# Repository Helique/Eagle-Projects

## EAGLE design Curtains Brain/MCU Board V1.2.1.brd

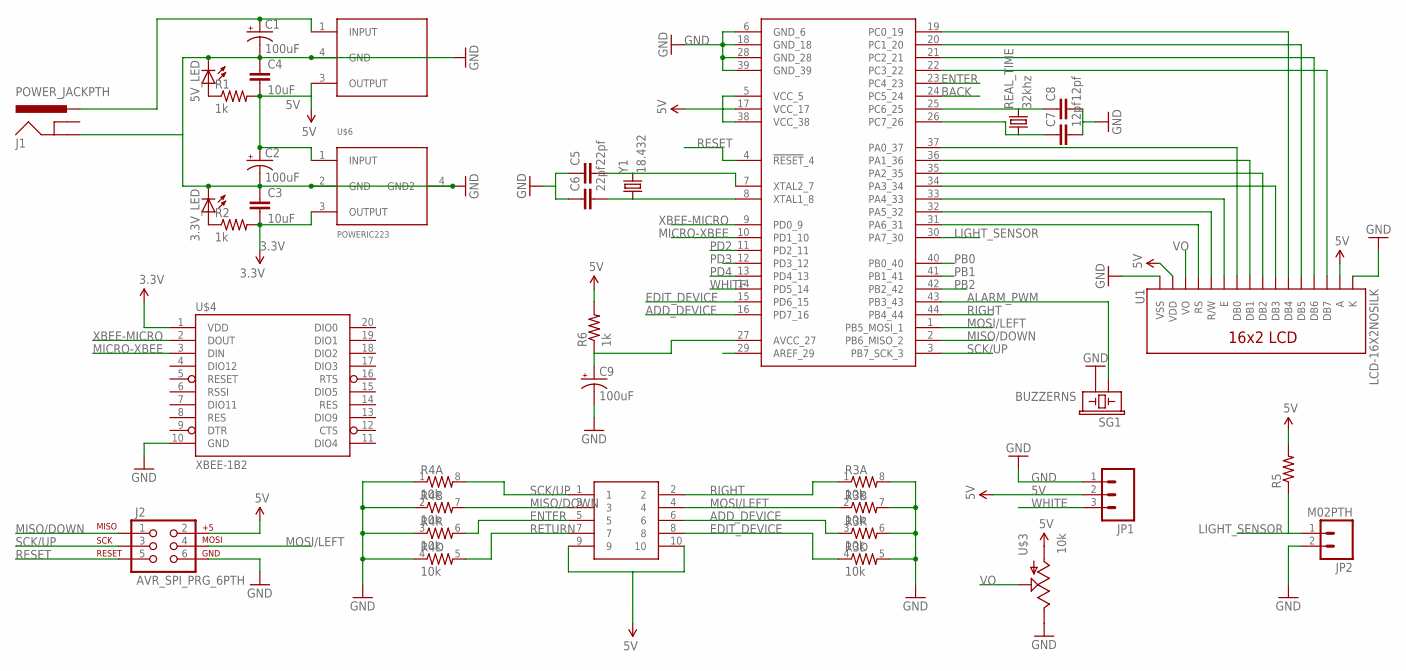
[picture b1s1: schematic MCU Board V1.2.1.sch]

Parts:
3.3V_LED, 5V_LED: LED1206; LED-1206
C1, C2, C9: 100uF; PANASONIC_D
C3, C4: 10uF; 1206
C5, C6: 22pf; 0805
C7, C8: 12pf; 0805
J1: POWER_JACKPTH; POWER_JACK_PTH
J2: AVR_SPI_PRG_6PTH; 2X3
JP1: M03PTH; 1X03
JP2: M02PTH; 1X02
R1, R2, R6: 1k; 1206
R3, R4: 10k; 0603-ARV
R5: RESISTOR1206; 1206
REAL_TIME: 32khz; TC26H
SG1: BUZZERNS; BUZZER-12MM-NS
U1: LCD-16X2NOSILK; LCD-16X2_NOSILK
U$1: ATMEGA1284; TQFP44
U$2: 10PIN_HEADER_MALETHROUGH-HOLE; 2X5-SHROUDED
U$3: 10k; TRIM_POT
U$4: XBEE-1B2; XBEE-SILK
U$5: DPACK_V_REG; DPAK
U$6: POWERIC223; SOT223
Y1: 18.432; HC49US

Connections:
3.3V: C3.2, R2.2, U$4.1 (VDD), U$6.3 (OUTPUT)
5V: C2.+, C4.2, J2.2, JP1.2, R1.2, R5.2, R6.2, U1.2 (VDD), U1.15 (A), U$1.5 (VCC_5), U$1.17 (VCC_17), U$1.38 (VCC_38), U$2.9, U$2.10, U$3.3 (A), U$5.3 (OUTPUT), U$6.1 (INPUT)
ADD_DEVICE: R3.3 (1), U$1.16 (PD7_16), U$2.6
ALARM_PWM: SG1.+ (1), U$1.43 (PB3_43)
AREF: U$1.29 (AREF_29)
BACK: U$1.24 (PC5_24)
EDIT_DEVICE: R3.4 (1), U$1.15 (PD6_15), U$2.8
ENTER: R4.6 (2), U$1.23 (PC4_23), U$2.5
GND: 3.3V_LED.C, 5V_LED.C, C1.-, C2.-, C3.1, C4.1, C5.1, C6.1, C7.2, C8.2, C9.-, J1.GND, J2.6, JP1.1, JP2.2, R3.5 (2), R3.6 (2), R3.7 (2), R3.8 (2), R4.1, R4.2 (1), R4.3 (1), R4.4 (1), SG1.- (2), U1.1 (VSS), U1.16 (K), U$1.6 (GND_6), U$1.18 (GND_18), U$1.28 (GND_28), U$1.39 (GND_39), U$3.2 (E), U$4.10 (GND), U$5.4 (GND), U$6.2 (GND), U$6.4 (GND2)
LIGHT_SENSOR: JP2.1, R5.1, U$1.30 (PA7_30)
MICRO-XBEE: U$1.10 (PD1_10), U$4.3 (DIN)
MISO/DOWN: J2.1, R4.7 (2), U$1.2 (PB6_MISO_2), U$2.3
MOSI/LEFT: J2.4, R3.2 (1), U$1.1 (PB5_MOSI_1), U$2.4
unnamed: C7.1, REAL_TIME.1, U$1.26 (PC7_26)
unnamed: C5.2, U$1.7 (XTAL2_7), Y1.2
unnamed: C6.2, U$1.8 (XTAL1_8), Y1.1
unnamed: C8.1, REAL_TIME.2, U$1.25 (PC6_25)
unnamed: 5V_LED.A, R1.1
unnamed: 3.3V_LED.A, R2.1
unnamed: U1.7 (DB0), U$1.37 (PA0_37)
unnamed: U1.8 (DB1), U$1.36 (PA1_36)
unnamed: U1.9 (DB2), U$1.35 (PA2_35)
unnamed: U1.10 (DB3), U$1.34 (PA3_34)
unnamed: U1.6 (E), U$1.33 (PA4_33)
unnamed: U1.5 (R/W), U$1.32 (PA5_32)
unnamed: U1.4 (RS), U$1.31 (PA6_31)
unnamed: U1.11 (DB4), U$1.19 (PC0_19)
unnamed: U1.12 (DB5), U$1.20 (PC1_20)
unnamed: U1.13 (DB6), U$1.21 (PC2_21)
unnamed: U1.14 (DB7), U$1.22 (PC3_22)
unnamed: C9.+, R6.1, U$1.27 (AVCC_27)
PB0: U$1.40 (PB0_40)
PB1: U$1.41 (PB1_41)
PB2: U$1.42 (PB2_42)
PD2: U$1.11 (PD2_11)
PD3: U$1.12 (PD3_12)
PD4: U$1.13 (PD4_13)
PWR: C1.+, J1.PWR, U$5.1 (INPUT)
RESET: J2.5, U$1.4 (!RESET!_4)
RETURN: R4.5 (2), U$2.7
RIGHT: R3.1, U$1.44 (PB4_44), U$2.2
SCK/UP: J2.3, R4.8 (2), U$1.3 (PB7_SCK_3), U$2.1
VO: U1.3 (VO), U$3.1 (S)
WHITE: JP1.3, U$1.14 (PD5_14)
XBEE-MICRO: U$1.9 (PD0_9), U$4.2 (DOUT)

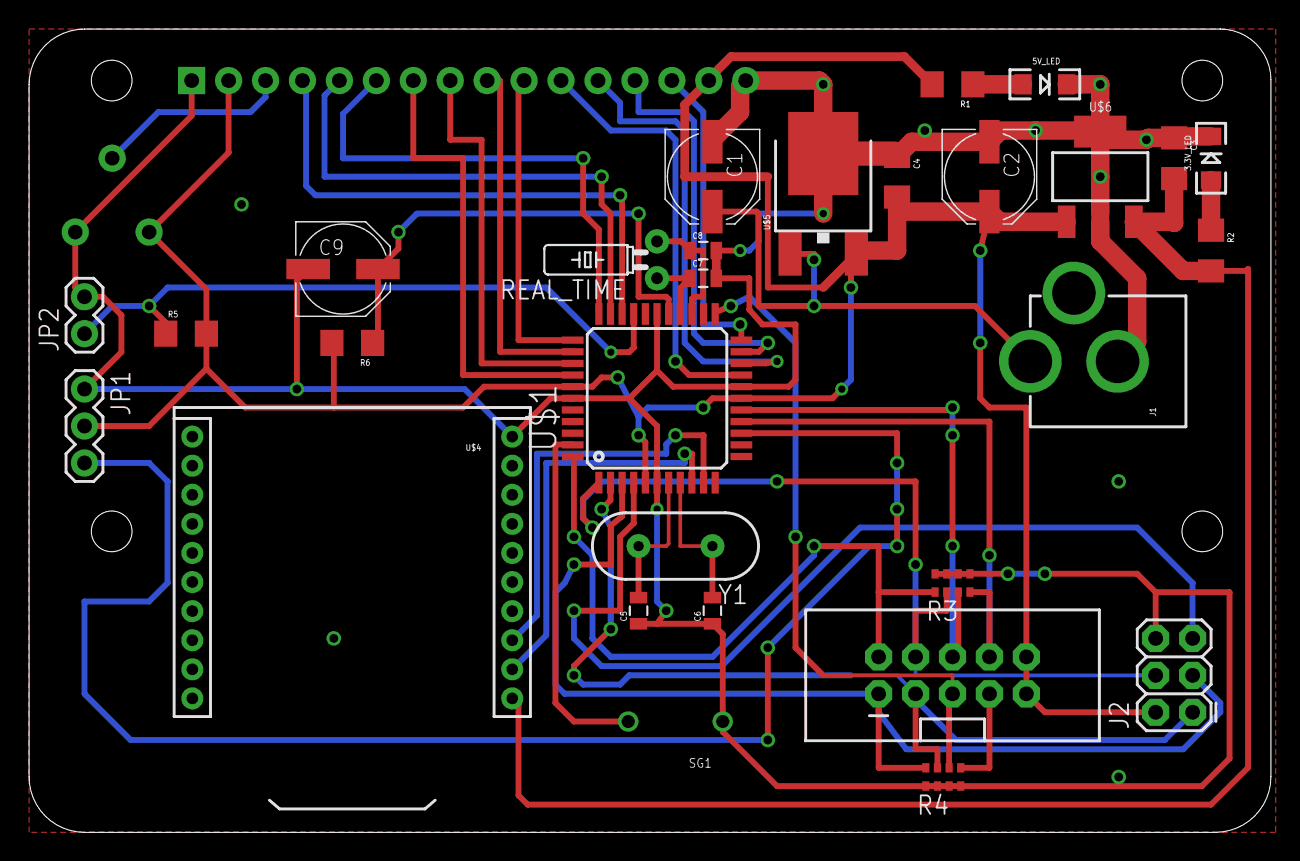
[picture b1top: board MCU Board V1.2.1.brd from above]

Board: 2 copper layers, 85.4 x 55.2 mm, 31 parts (0 on the bottom side), 37 nets.

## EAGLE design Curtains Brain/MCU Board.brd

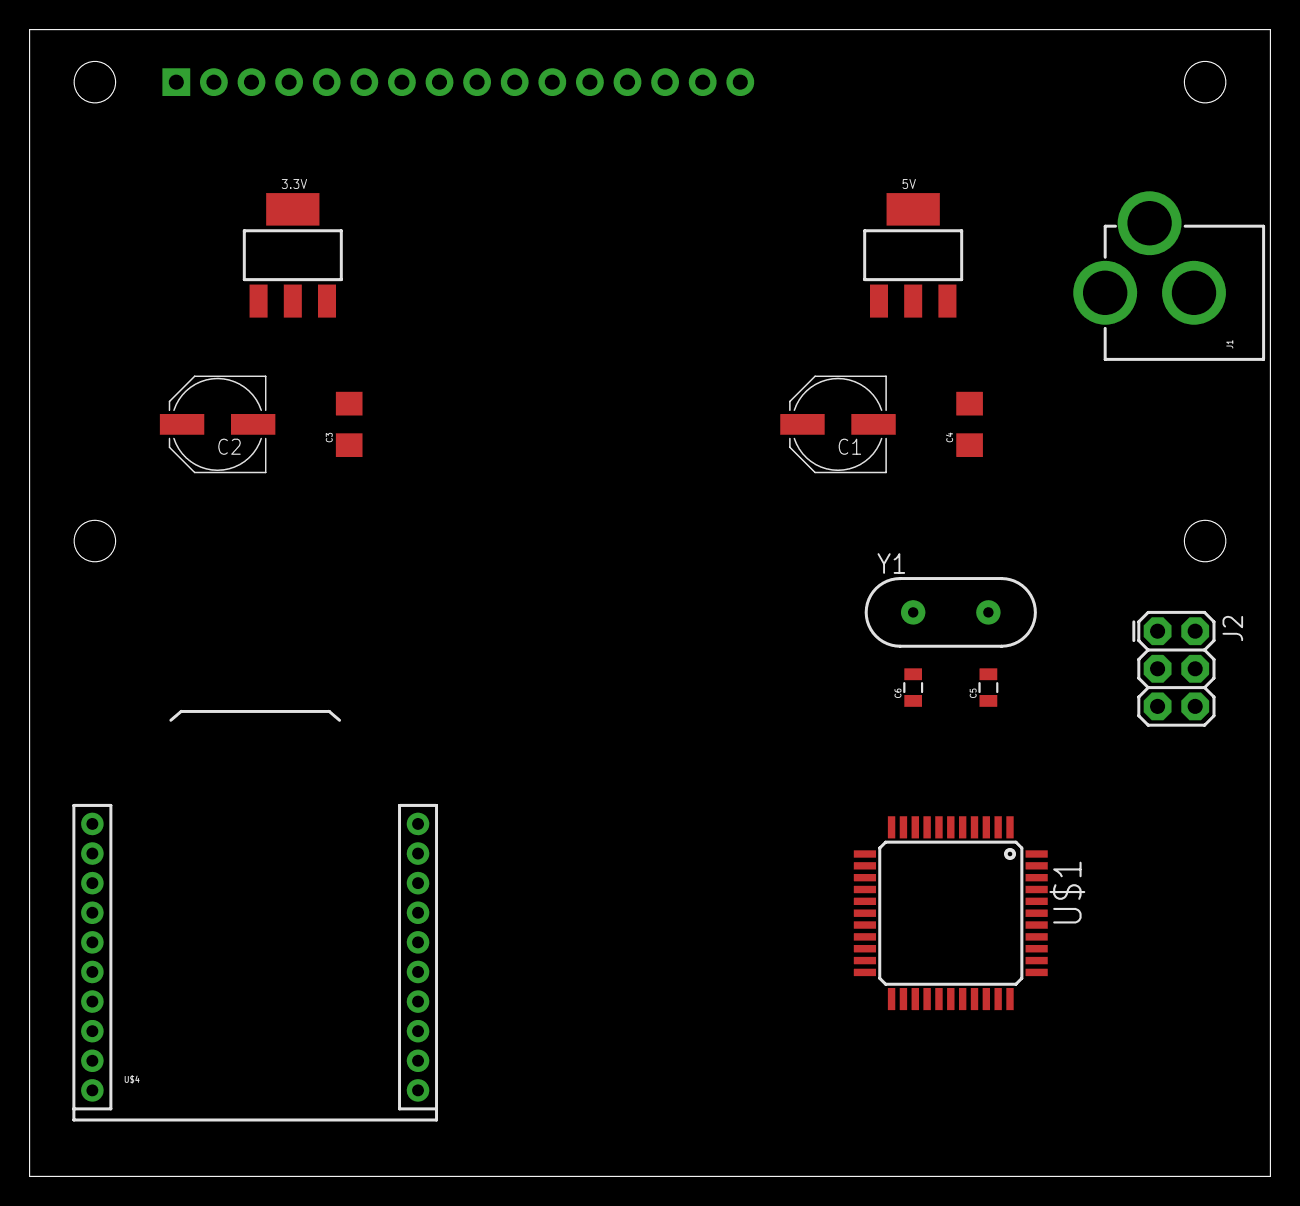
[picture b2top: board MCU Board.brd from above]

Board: 2 copper layers, 83.8 x 77.5 mm, 14 parts (0 on the bottom side), 12 nets, no tracks yet.

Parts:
3.3V, 5V: POWERIC223; SOT223
C1, C2: 100uF; PANASONIC_D
C3, C4: 10uF; 1206
C5, C6: 0805
J1: POWER_JACKPTH; POWER_JACK_PTH
J2: AVR_SPI_PRG_6PTH; 2X3
U1: LCD-16X2NOSILK; LCD-16X2_NOSILK
U$1: ATMEGA1284; TQFP44
U$4: XBEE-1B2; XBEE-SILK
Y1: HC49US

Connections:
3.3V: 3.3V.3, C3.2, U$4.1
5V: 5V.3, C4.2, J2.2, U$1.5, U$1.17, U$1.38
DIN: U$1.9, U$4.3
DOUT: U$1.10, U$4.2
GND: 3.3V.2, 3.3V.4, 5V.2, 5V.4, C1.-, C2.-, C3.1, C4.1, C5.1, C6.1, J1.GND, J2.6, U$1.6, U$1.18, U$1.28, U$1.39, U$4.10
MISO: J2.1, U$1.2
MOSI: J2.4, U$1.1
unnamed: C5.2, U$1.7, Y1.2
unnamed: C6.2, U$1.8, Y1.1
PWR: 3.3V.1, 5V.1, C1.+, C2.+, J1.PWR
RESET: J2.5, U$1.4
SCK: J2.3, U$1.3

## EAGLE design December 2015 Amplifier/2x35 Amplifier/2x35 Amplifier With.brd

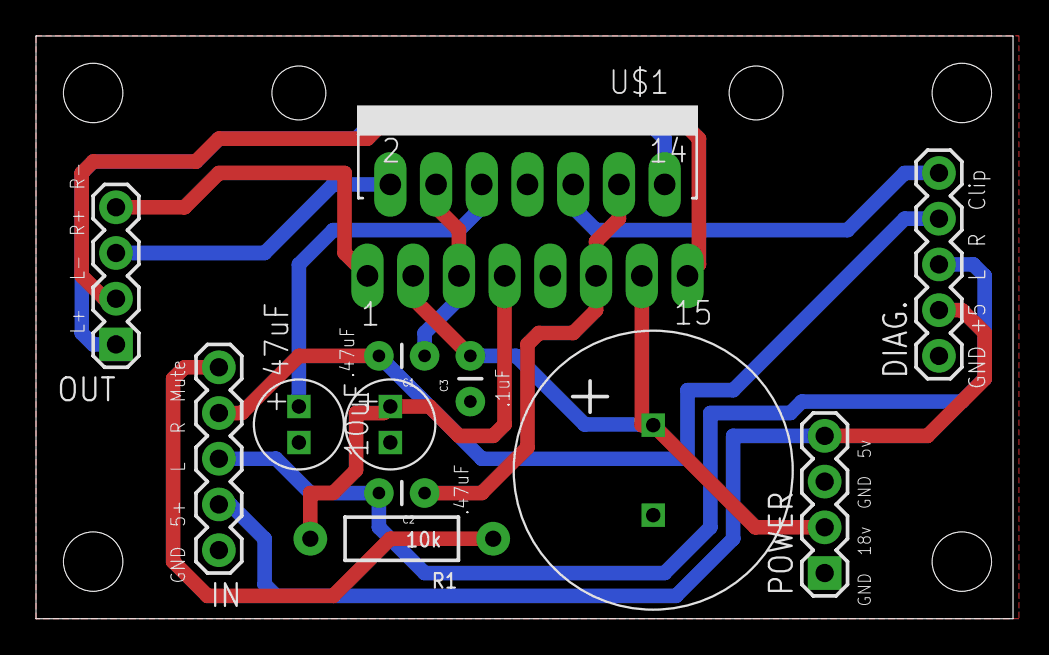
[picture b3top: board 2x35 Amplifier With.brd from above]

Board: 2 copper layers, 54.3 x 32.4 mm, 17 parts (0 on the bottom side), 15 nets.

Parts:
10UF, 47UF: 5MM-12.5MM-POLAR2MMX5MM; 2MMLEAD_5MMDIAMETER
1000UF: 5MM-12.5MM-POLAR5MMX12.5MM; 5MMLEAD_12.5MMDIAMETER
C1, C2: .47uF; CAP-PTH-SMALL
C3: .1uF; CAP-PTH-SMALL
DIAG.: 1X05
IN: 1X05
OUT: 1X04
POWER: 1X04
R1: 10k; AXIAL-0.4
U$1: TDA7375V; MULTIWATT-15
U$2: 6400BG_HEATSINK
U$3, U$4, U$5, U$6: STAND-OFF

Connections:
+5V: DIAG..2, IN.2, POWER.4
CLIP: DIAG..5, U$1.10
GND: 10UF.-, 47UF.-, 1000UF.-, C3.1, DIAG..1, IN.1, POWER.1, POWER.3, U$1.8, U$1.9
IN1: C1.1, U$1.4, U$1.5
IN3: C2.1, U$1.11, U$1.12
unnamed: 10UF.+, R1.P$2, U$1.7
unnamed: 47UF.+, U$1.6
OUT1: OUT.4, U$1.1
OUT2: OUT.3, U$1.2
OUT3: OUT.2, U$1.15
OUT4: OUT.1, U$1.14
RAW_IN1: C1.2, DIAG..4, IN.4
RAW_IN3: C2.2, DIAG..3, IN.3
ST-BY: IN.5, R1.P$1
VCC: 1000UF.+, C3.2, POWER.2, U$1.3, U$1.13

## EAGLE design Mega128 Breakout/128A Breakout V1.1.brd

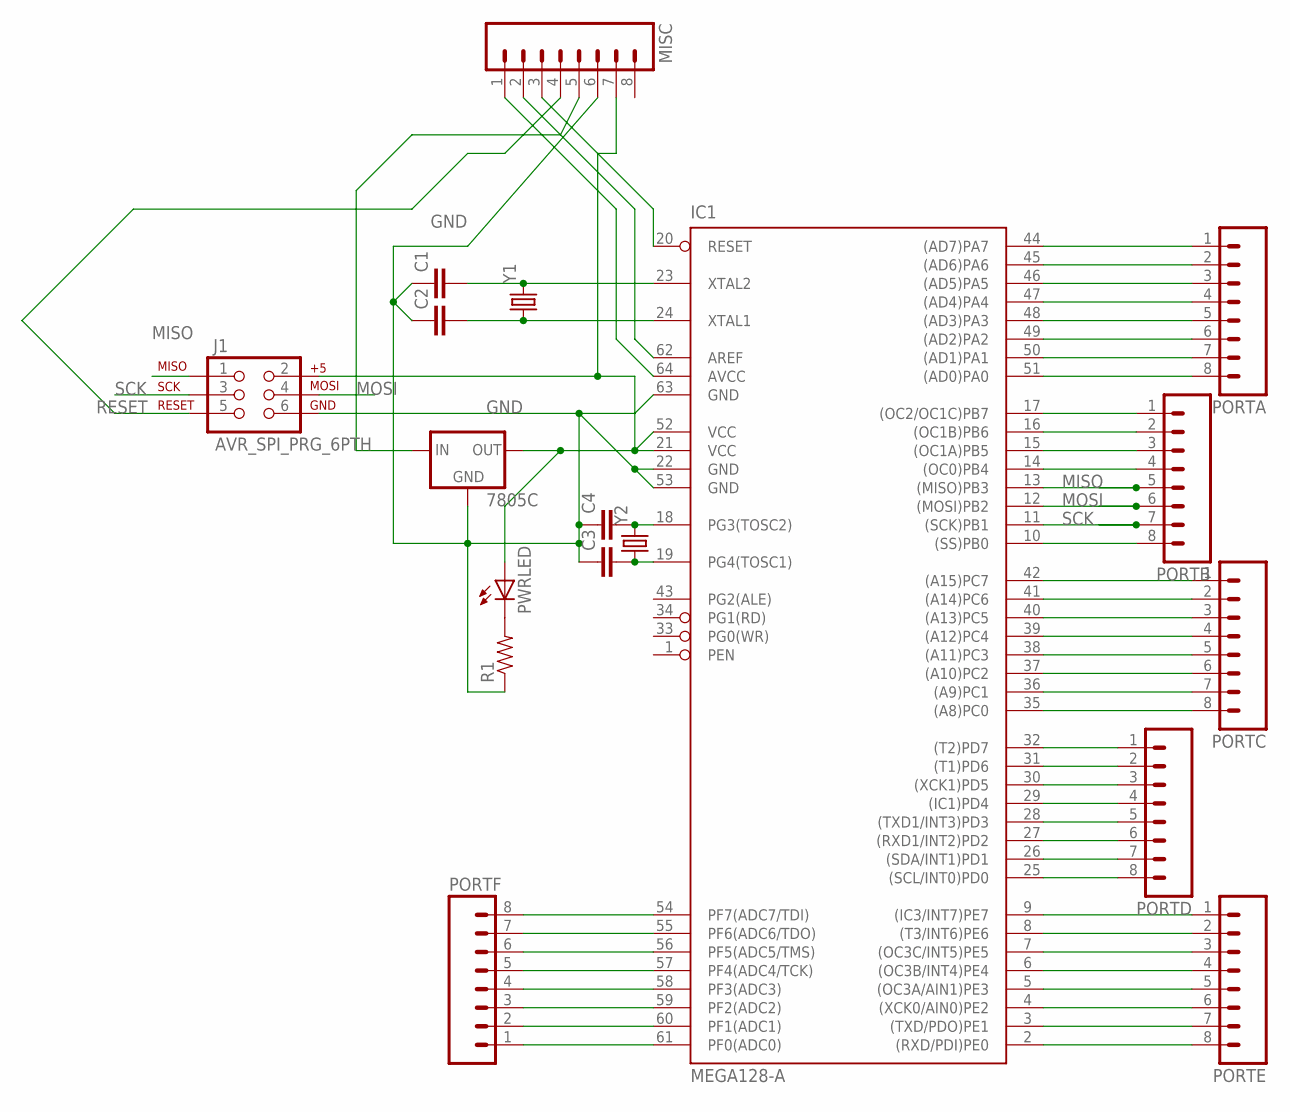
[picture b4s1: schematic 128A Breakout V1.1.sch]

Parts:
7805C: V_REG_78XXSIDE; 78XXL
C1, C2, C3, C4: CAP1206; 1206
IC1: MEGA128-A; TQFP64
J1: AVR_SPI_PRG_6PTH; 2X3
MISC: M081X08; 1X08
PORTA: M081X08; 1X08
PORTB: M081X08; 1X08
PORTC: M081X08; 1X08
PORTD: M081X08; 1X08
PORTE: M081X08; 1X08
PORTF: M081X08; 1X08
PWRLED: LED-FKIT-1206; FKIT-LED-1206
R1: RESISTOR1206; 1206
Y1: CRYSTALHC49US; HC49US
Y2: CRYSTALTC26H_EZ; TC26HEZ

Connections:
5V: 7805C.OUT, IC1.21 (VCC), IC1.52 (VCC), J1.2, MISC.7, PWRLED.A
GND: 7805C.GND, C1.1, C2.1, C3.1, C4.1, IC1.22 (GND), IC1.53 (GND), IC1.63 (GND), J1.6, MISC.6, R1.1
MISO: IC1.13 ((MISO)PB3), J1.1, PORTB.5
MOSI: IC1.12 ((MOSI)PB2), J1.4, PORTB.6
unnamed: IC1.54 (PF7(ADC7/TDI)), PORTF.8
unnamed: C4.2, IC1.18 (PG3(TOSC2)), Y2.2
unnamed: C2.2, IC1.24 (XTAL1), Y1.1
unnamed: C1.2, IC1.23 (XTAL2), Y1.2
unnamed: IC1.55 (PF6(ADC6/TDO)), PORTF.7
unnamed: C3.2, IC1.19 (PG4(TOSC1)), Y2.1
unnamed: IC1.56 (PF5(ADC5/TMS)), PORTF.6
unnamed: IC1.57 (PF4(ADC4/TCK)), PORTF.5
unnamed: IC1.58 (PF3(ADC3)), PORTF.4
unnamed: IC1.59 (PF2(ADC2)), PORTF.3
unnamed: IC1.60 (PF1(ADC1)), PORTF.2
unnamed: IC1.61 (PF0(ADC0)), PORTF.1
unnamed: IC1.9 ((IC3/INT7)PE7), PORTE.1
unnamed: IC1.8 ((T3/INT6)PE6), PORTE.2
unnamed: IC1.7 ((OC3C/INT5)PE5), PORTE.3
unnamed: IC1.6 ((OC3B/INT4)PE4), PORTE.4
unnamed: IC1.5 ((OC3A/AIN1)PE3), PORTE.5
unnamed: IC1.4 ((XCK0/AIN0)PE2), PORTE.6
unnamed: IC1.3 ((TXD/PDO)PE1), PORTE.7
unnamed: IC1.2 ((RXD/PDI)PE0), PORTE.8
unnamed: IC1.32 ((T2)PD7), PORTD.1
unnamed: IC1.31 ((T1)PD6), PORTD.2
unnamed: IC1.30 ((XCK1)PD5), PORTD.3
unnamed: IC1.29 ((IC1)PD4), PORTD.4
unnamed: IC1.28 ((TXD1/INT3)PD3), PORTD.5
unnamed: IC1.27 ((RXD1/INT2)PD2), PORTD.6
unnamed: IC1.26 ((SDA/INT1)PD1), PORTD.7
unnamed: IC1.25 ((SCL/INT0)PD0), PORTD.8
unnamed: IC1.42 ((A15)PC7), PORTC.1
unnamed: IC1.41 ((A14)PC6), PORTC.2
unnamed: IC1.40 ((A13)PC5), PORTC.3
unnamed: IC1.39 ((A12)PC4), PORTC.4
unnamed: IC1.38 ((A11)PC3), PORTC.5
unnamed: IC1.37 ((A10)PC2), PORTC.6
unnamed: IC1.36 ((A9)PC1), PORTC.7
unnamed: IC1.35 ((A8)PC0), PORTC.8
unnamed: IC1.17 ((OC2/OC1C)PB7), PORTB.1
unnamed: IC1.16 ((OC1B)PB6), PORTB.2
unnamed: IC1.15 ((OC1A)PB5), PORTB.3
unnamed: IC1.14 ((OC0)PB4), PORTB.4
unnamed: IC1.10 ((SS)PB0), PORTB.8
unnamed: IC1.44 ((AD7)PA7), PORTA.1
unnamed: IC1.45 ((AD6)PA6), PORTA.2
unnamed: IC1.46 ((AD5)PA5), PORTA.3
unnamed: IC1.47 ((AD4)PA4), PORTA.4
unnamed: IC1.48 ((AD3)PA3), PORTA.5
unnamed: IC1.49 ((AD2)PA2), PORTA.6
unnamed: IC1.50 ((AD1)PA1), PORTA.7
unnamed: IC1.51 ((AD0)PA0), PORTA.8
unnamed: IC1.64 (AVCC), MISC.1
unnamed: IC1.62 (AREF), MISC.2
unnamed: IC1.20 (RESET), MISC.3
unnamed: PWRLED.C, R1.2
RESET: J1.5, MISC.4
SCK: IC1.11 ((SCK)PB1), J1.3, PORTB.7
VIN: 7805C.IN, MISC.5

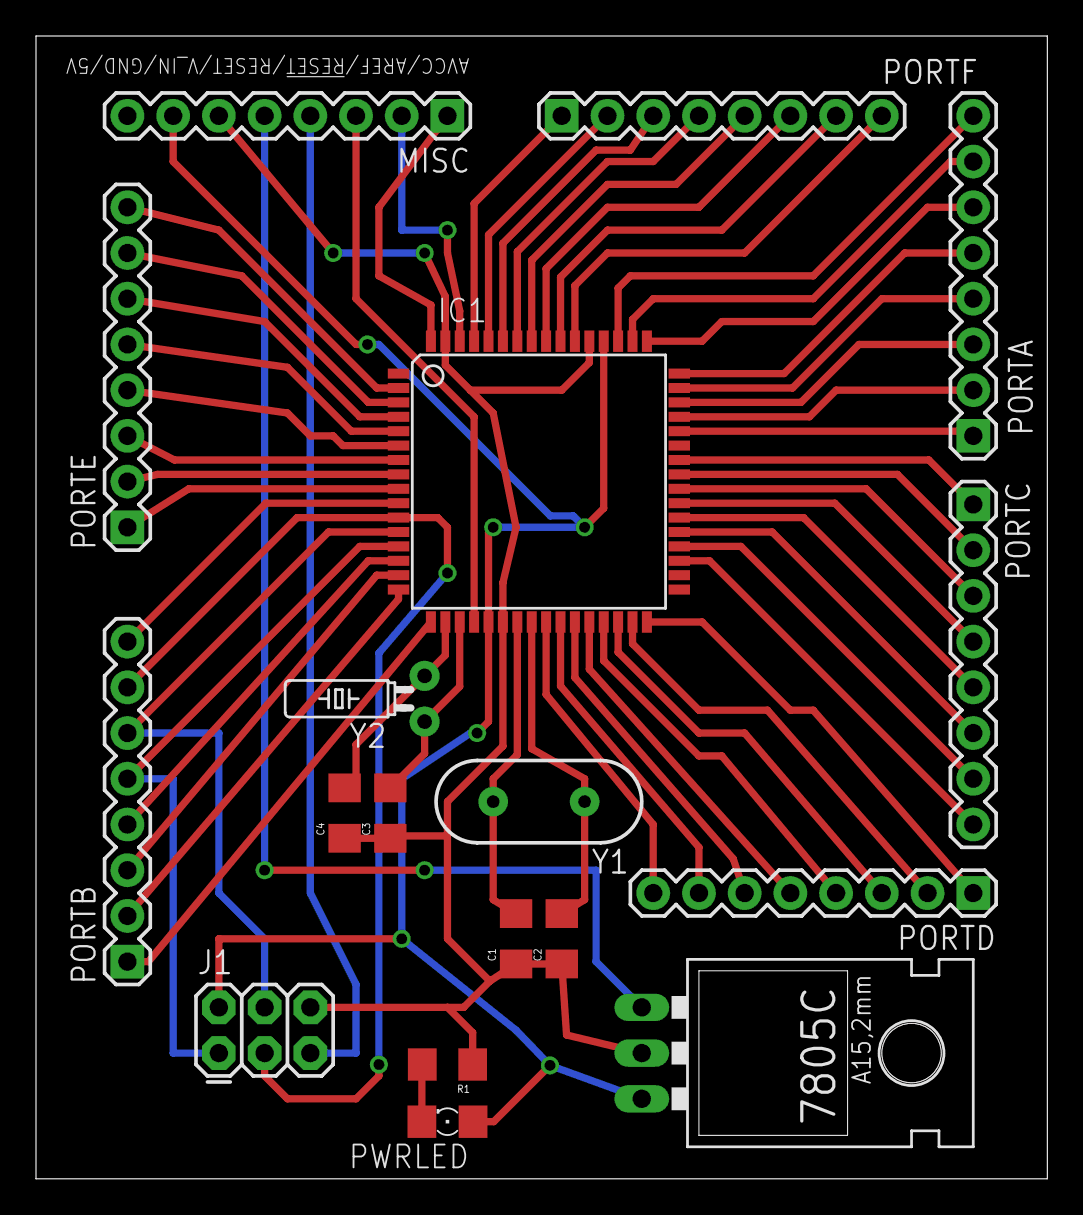
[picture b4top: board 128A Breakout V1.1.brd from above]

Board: 2 copper layers, 56.2 x 63.5 mm, 18 parts (0 on the bottom side), 60 nets.

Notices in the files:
parts and their libraries:
SparkFun-Displays: Licensing: CC v3.0 Share-Alike You are welcome to use this library for commercial purposes.
